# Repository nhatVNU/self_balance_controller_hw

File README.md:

# self_balance_controller_hw

PCB:

3D:

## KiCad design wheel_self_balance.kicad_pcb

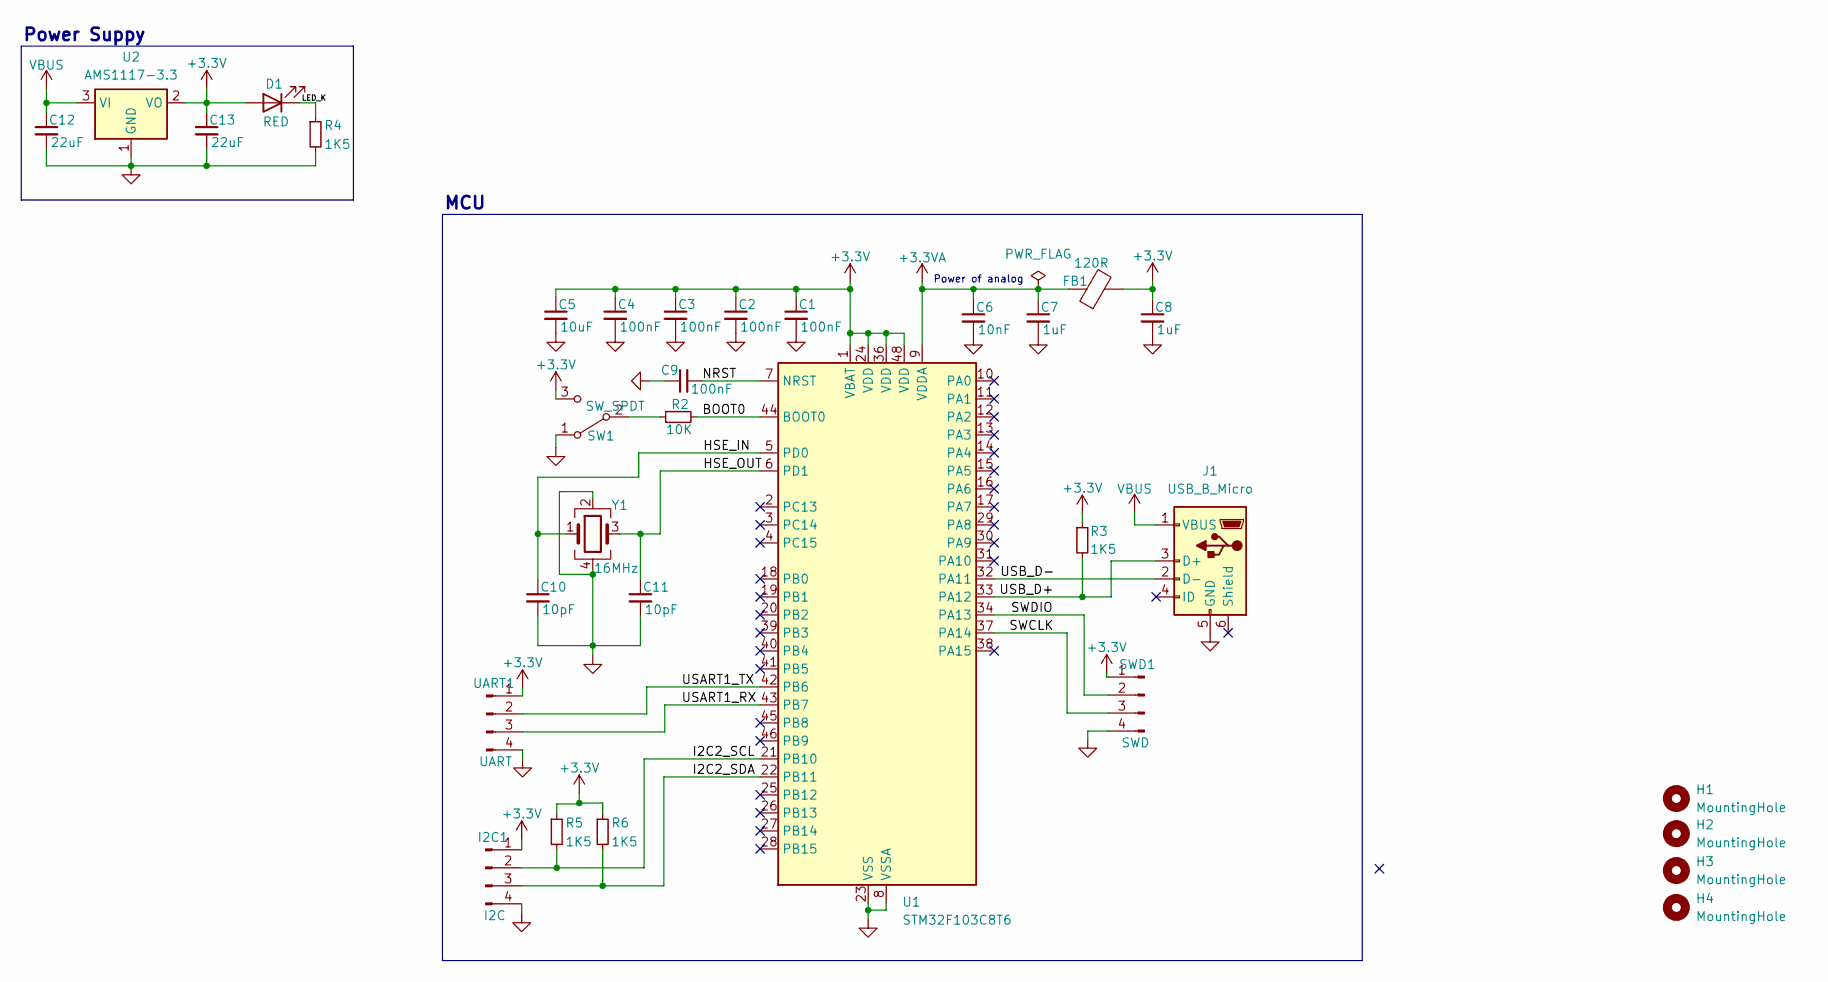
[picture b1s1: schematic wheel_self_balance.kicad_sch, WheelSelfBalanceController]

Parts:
C1, C2, C3, C4, C9: 100nF; C_0402_1005Metric
C5: 10uF; C_0603_1608Metric
C6: 10nF; C_0402_1005Metric
C7, C8: 1uF; C_0402_1005Metric
C10, C11: 10pF; C_0402_1005Metric
C12, C13: 22uF; C_0805_2012Metric
D1: RED; LED_0603_1608Metric
FB1: 120R; L_0603_1608Metric
H1, H2, H3, H4: MountingHole; MountingHole_2.2mm_M2
I2C1: I2C; PinHeader_1x04_P2.54mm_Vertical
J1: USB_B_Micro; USB_Micro-B_Wuerth_629105150521
R2: 10K; R_0402_1005Metric
R3, R4, R5, R6: 1K5; R_0402_1005Metric
SW1: SW_SPDT; SW_SPDT_PCM12
SWD1: SWD; PinHeader_1x04_P2.54mm_Vertical
U1: STM32F103C8T6; LQFP-48_7x7mm_P0.5mm
U2: AMS1117-3.3; SOT-223-3_TabPin2
UART1: UART; PinHeader_1x04_P2.54mm_Vertical
Y1: 16MHz; Crystal_SMD_3225-4Pin_3.2x2.5mm

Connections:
+3.3V: C1.1, C2.1, C3.1, C4.1, C5.1, C8.1, C13.1, D1.2 (A), FB1.2, I2C1.1, R3.1, R5.1, R6.1, SW1.3 (C), SWD1.1, U1.1 (VBAT), U1.24 (VDD), U1.36 (VDD), U1.48 (VDD), U2.2 (VO), UART1.1
+3.3VA: C6.1, C7.1, FB1.1, U1.9 (VDDA)
/BOOT0: R2.2, U1.44 (BOOT0)
/HSE_IN: C10.1, U1.5 (PD0), Y1.1
/HSE_OUT: C11.1, U1.6 (PD1), Y1.3
/I2C2_SCL: I2C1.2, R5.2, U1.21 (PB10)
/I2C2_SDA: I2C1.3, R6.2, U1.22 (PB11)
/LED_K: D1.1 (K), R4.1
/NRST: C9.2, U1.7 (NRST)
/SWCLK: SWD1.3, U1.37 (PA14)
/SWDIO: SWD1.2, U1.34 (PA13)
/USART1_RX: U1.43 (PB7), UART1.3
/USART1_TX: U1.42 (PB6), UART1.2
/USB_D+: J1.3 (D+), R3.2, U1.33 (PA12)
/USB_D-: J1.2 (D-), U1.32 (PA11)
GND: C1.2, C2.2, C3.2, C4.2, C5.2, C6.2, C7.2, C8.2, C9.1, C10.2, C11.2, C12.2, C13.2, I2C1.4, J1.5 (GND), R4.2, SW1.1 (A), SWD1.4, U1.8 (VSSA), U1.23 (VSS), U1.35 (VSS), U1.47 (VSS), U2.1 (GND), UART1.4, Y1.2, Y1.4
unnamed: R2.1, SW1.2 (B)
VBUS: C12.1, J1.1 (VBUS), U2.3 (VI)

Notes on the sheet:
Power of analog
Power Suppy
MCU

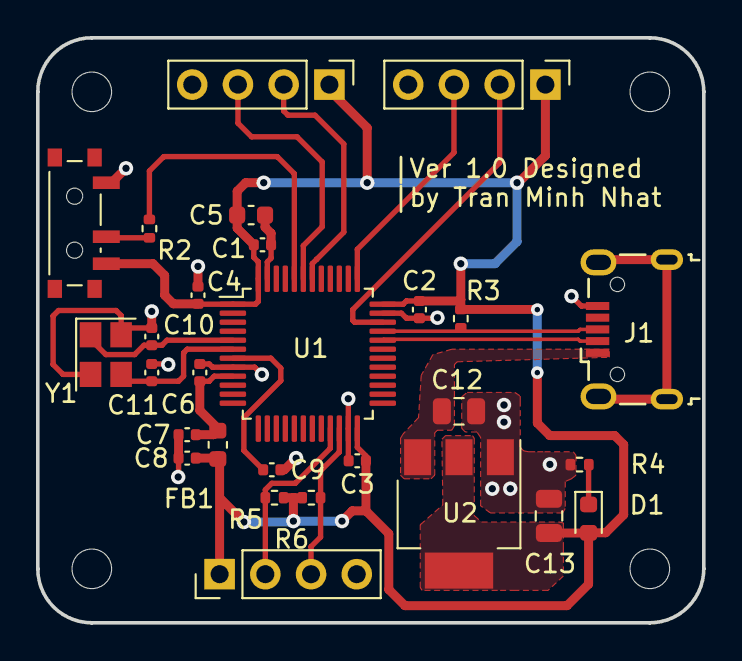
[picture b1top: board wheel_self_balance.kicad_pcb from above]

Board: 2 copper layers, 37.0 x 32.5 mm, 32 parts (0 on the bottom side), 18 nets.

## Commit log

2024-03-03 Upload version 1.0
2024-03-03 Update image for readme
2024-03-03 Restore schematic file
